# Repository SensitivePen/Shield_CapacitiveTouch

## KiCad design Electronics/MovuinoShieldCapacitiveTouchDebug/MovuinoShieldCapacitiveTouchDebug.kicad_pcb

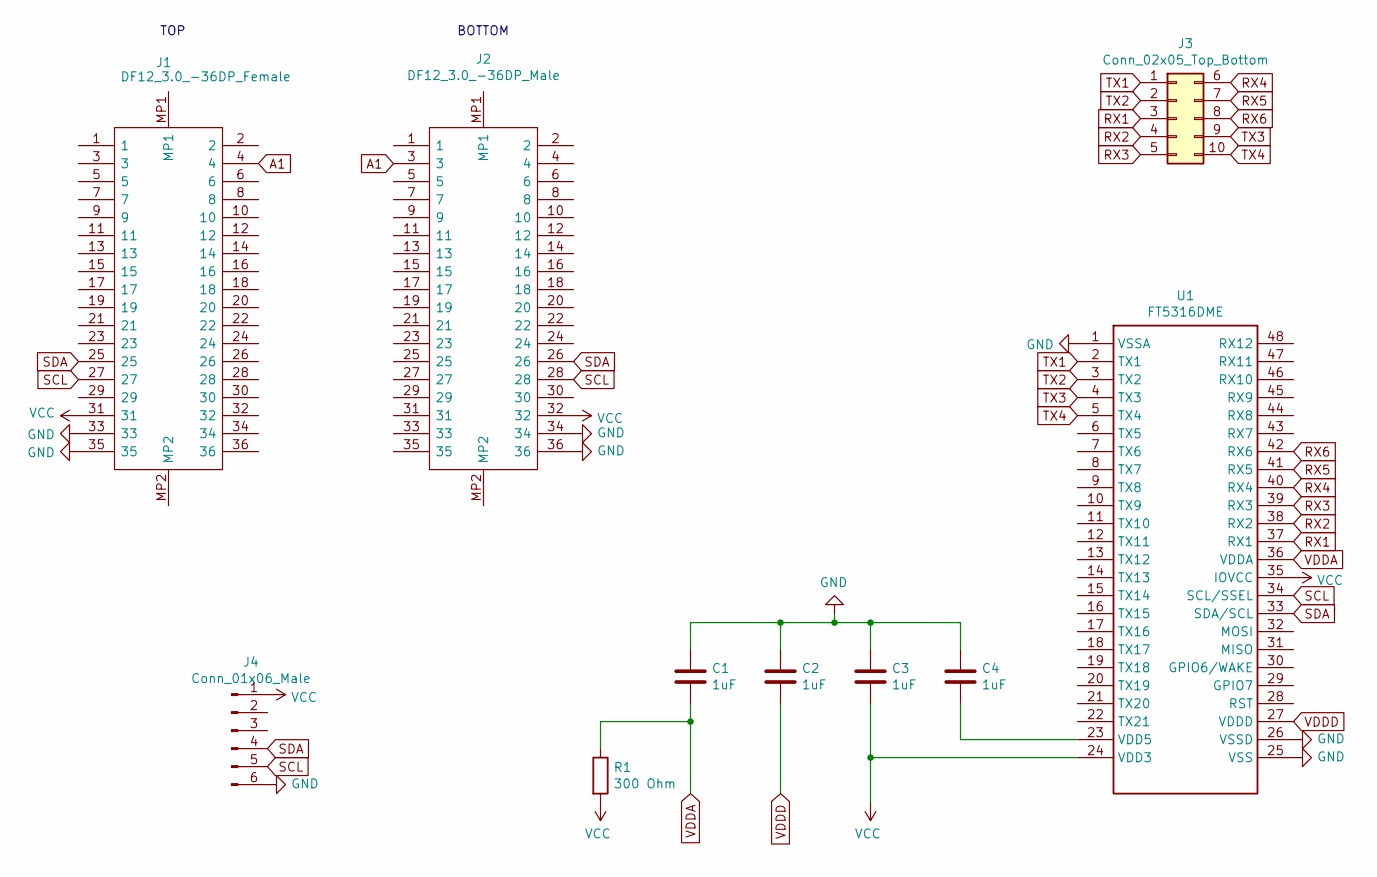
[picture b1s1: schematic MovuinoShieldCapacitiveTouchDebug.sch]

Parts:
C1, C2, C3, C4: 1uF; C_0603_1608Metric
J1: DF12_3.0_-36DP_Female; DF123036DP05V86; Mouser Part Number 798-DF123036DP0.5V86
J2: DF12_3.0_-36DP_Male; DF123036DP05V86; Mouser Part Number 798-DF123036DP0.5V86
J3: Conn_02x05_Top_Bottom; PinSocket_2x05_P2.54mm_Vertical
J4: Conn_01x06_Male; PinHeader_1x06_P2.54mm_Vertical
R1: 300 Ohm; R_0603_1608Metric
U1: FT5316DME; QFN40P600X600X60-49N

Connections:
A1: J1.4, J2.3
GND: C1.1, C2.1, C3.1, C4.1, J1.33, J1.35, J2.34, J2.36, J4.6, U1.1 (VSSA), U1.25 (VSS), U1.26 (VSSD)
unnamed: C4.2, U1.23 (VDD5)
RX1: J3.3, U1.37 (RX1)
RX2: J3.4, U1.38 (RX2)
RX3: J3.5, U1.39 (RX3)
RX4: J3.6, U1.40 (RX4)
RX5: J3.7, U1.41 (RX5)
RX6: J3.8, U1.42 (RX6)
SCL: J1.27, J2.28, J4.5, U1.34 (SCL/SSEL)
SDA: J1.25, J2.26, J4.4, U1.33 (SDA/SCL)
TX1: J3.1, U1.2 (TX1)
TX2: J3.2, U1.3 (TX2)
TX3: J3.9, U1.4 (TX3)
TX4: J3.10, U1.5 (TX4)
VCC: C3.2, J1.31, J2.32, J4.1, R1.2, U1.24 (VDD3), U1.35 (IOVCC)
VDDA: C1.2, R1.1, U1.36 (VDDA)
VDDD: C2.2, U1.27 (VDDD)

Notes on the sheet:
TOP
BOTTOM

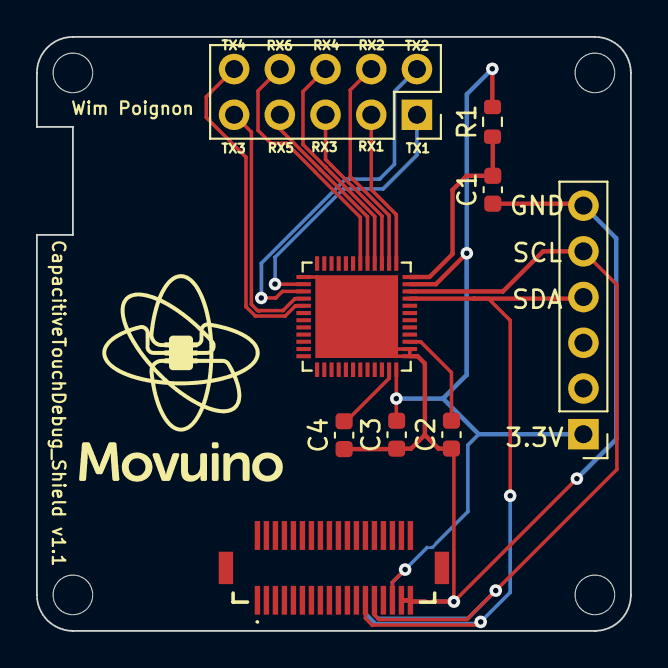
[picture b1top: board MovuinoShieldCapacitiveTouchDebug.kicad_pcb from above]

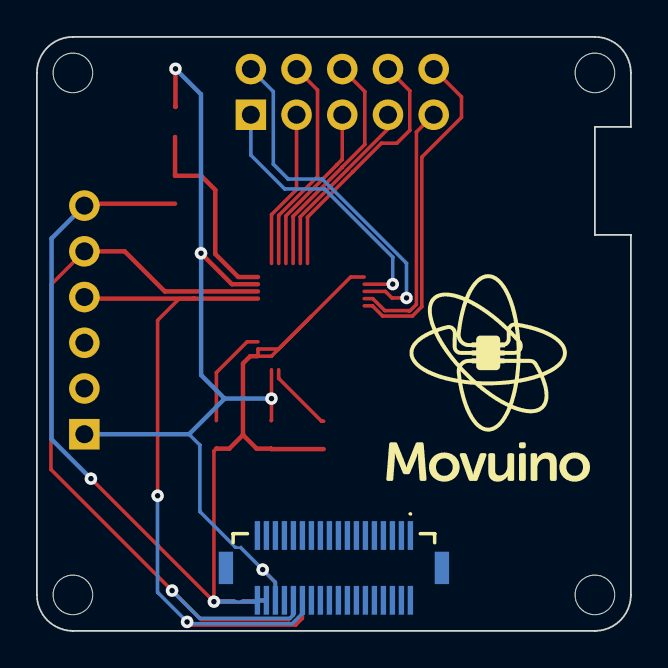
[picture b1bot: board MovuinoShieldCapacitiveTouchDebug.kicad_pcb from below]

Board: 2 copper layers, 33.0 x 33.0 mm, 12 parts (2 on the bottom side), 18 nets.

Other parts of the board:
U$8, U$8#2: LOGO_MOVUINOBOTTOM_11MM; LOGO_MOVUINO_BMP_11MM-BOTTOM

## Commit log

2022-04-13 init gitignore
2022-04-13 init electronics
2022-04-13 init FT5316
2022-04-13 init CapacitiveTouch_Raw
2022-04-14 rename directory
2022-04-20 add TouchPointsProcessing image
2022-04-20 init CapacitiveTouch_TouchPoints
2022-04-26 fix(lib): CapacitiveTouch
2022-04-26 fix(dataviz): TouchPoint
2022-04-26 fix(lib): CapacitivTouch
    invert rx tx
2022-04-26 fix: invert rx tx
2022-04-26 feat(add): ComputerVision to Raw data
2022-05-02 Move ComputerVision
2022-05-02 add Python ignore
2022-05-02 init ComputerVision Python
2022-05-02 fix(baudrate)
2022-05-03 feat(serial_port): ComputerVision Python
2022-05-03 fix(exception)
2022-05-03 feat(add): requirements lib
2022-05-03 clean repo
2022-05-03 add Raw_AutoCalibration
2022-05-05 fix(lib): SDA/SCL ESP32
2022-05-05 rename
2022-05-09 feat(figure): ComputerVision Python
2022-05-10 add record data
2022-05-10 fix(speed)
2022-05-10 add contour_detection
2022-05-11 feat(contour): center position
2022-05-13 change threshold
2022-05-23 add contour and image classes
2022-05-23 fix(filename): .txt or .npy
2022-05-25 feat(comments): Image class
2022-06-07 add record data ESP32
2022-06-10 add CapacitiveTouch Sensor
2022-06-14 feat(shielding layer): CapacitiveTouch Sensor
2022-07-21 Add example OnePoint_Stream
2022-07-22 Add example OnePoint_Record
2022-07-26 Add spiff extraction from movuino to computer
